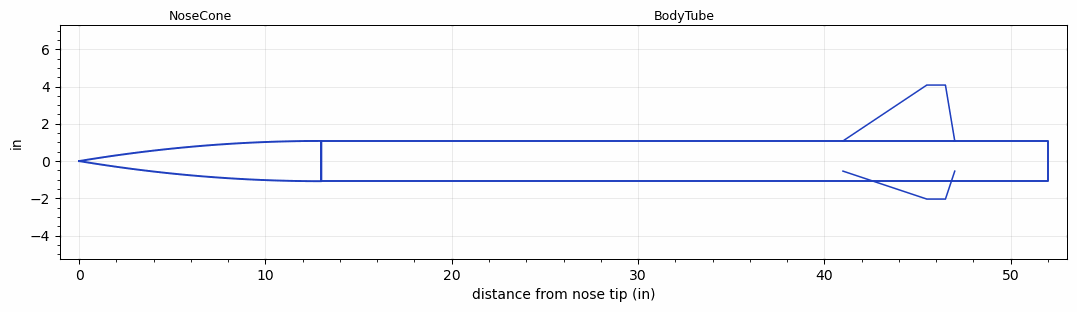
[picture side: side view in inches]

<RASAeroDocument>
 <FileVersion>2</FileVersion>
 <RocketDesign>
  <NoseCone>
   <Length>13</Length>
   <Diameter>2.16</Diameter>
   <Shape>Parabolic</Shape>
   <Location>0</Location>
  </NoseCone>
  <BodyTube>
   <Length>39</Length>
   <Diameter>2.16</Diameter>
   <Location>13</Location>
   <Fin>
    <Count>3</Count>
    <Chord>6</Chord>
    <Span>3</Span>
    <SweepDistance>4.5</SweepDistance>
    <TipChord>1</TipChord>
    <Thickness>0.07</Thickness>
    <Location>11</Location>
    <AirfoilSection>Rounded</AirfoilSection>
   </Fin>
  </BodyTube>
  <Surface>Camouflage Paint</Surface>
  <ModifiedBarrowman>False</ModifiedBarrowman>
  <Turbulence>False</Turbulence>
  <UseBooster1>False</UseBooster1>
  <UseBooster2>False</UseBooster2>
 </RocketDesign>
 <LaunchSite>
  <Altitude>5000</Altitude>
  <Pressure>0</Pressure>
  <RodAngle>7</RodAngle>
  <RodLength>18</RodLength>
  <Temperature>95</Temperature>
  <WindSpeed>8</WindSpeed>
 </LaunchSite>
 <Recovery>
  <Altitude1>1000</Altitude1>
  <Altitude2>1500</Altitude2>
  <DeviceType1>Parachute</DeviceType1>
  <DeviceType2>Parachute</DeviceType2>
  <Event1>True</Event1>
  <Event2>True</Event2>
  <Size1>30.57</Size1>
  <Size2>96</Size2>
  <EventType1>Apogee</EventType1>
  <EventType2>Altitude</EventType2>
  <CD1>0.75</CD1>
  <CD2>2.2</CD2>
 </Recovery>
</RASAeroDocument>
